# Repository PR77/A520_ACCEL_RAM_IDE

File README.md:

# A520_ACCEL_RAM_IDE
Amiga 500 in socket 68020 Accelerator, FastRAM and IDE Interface

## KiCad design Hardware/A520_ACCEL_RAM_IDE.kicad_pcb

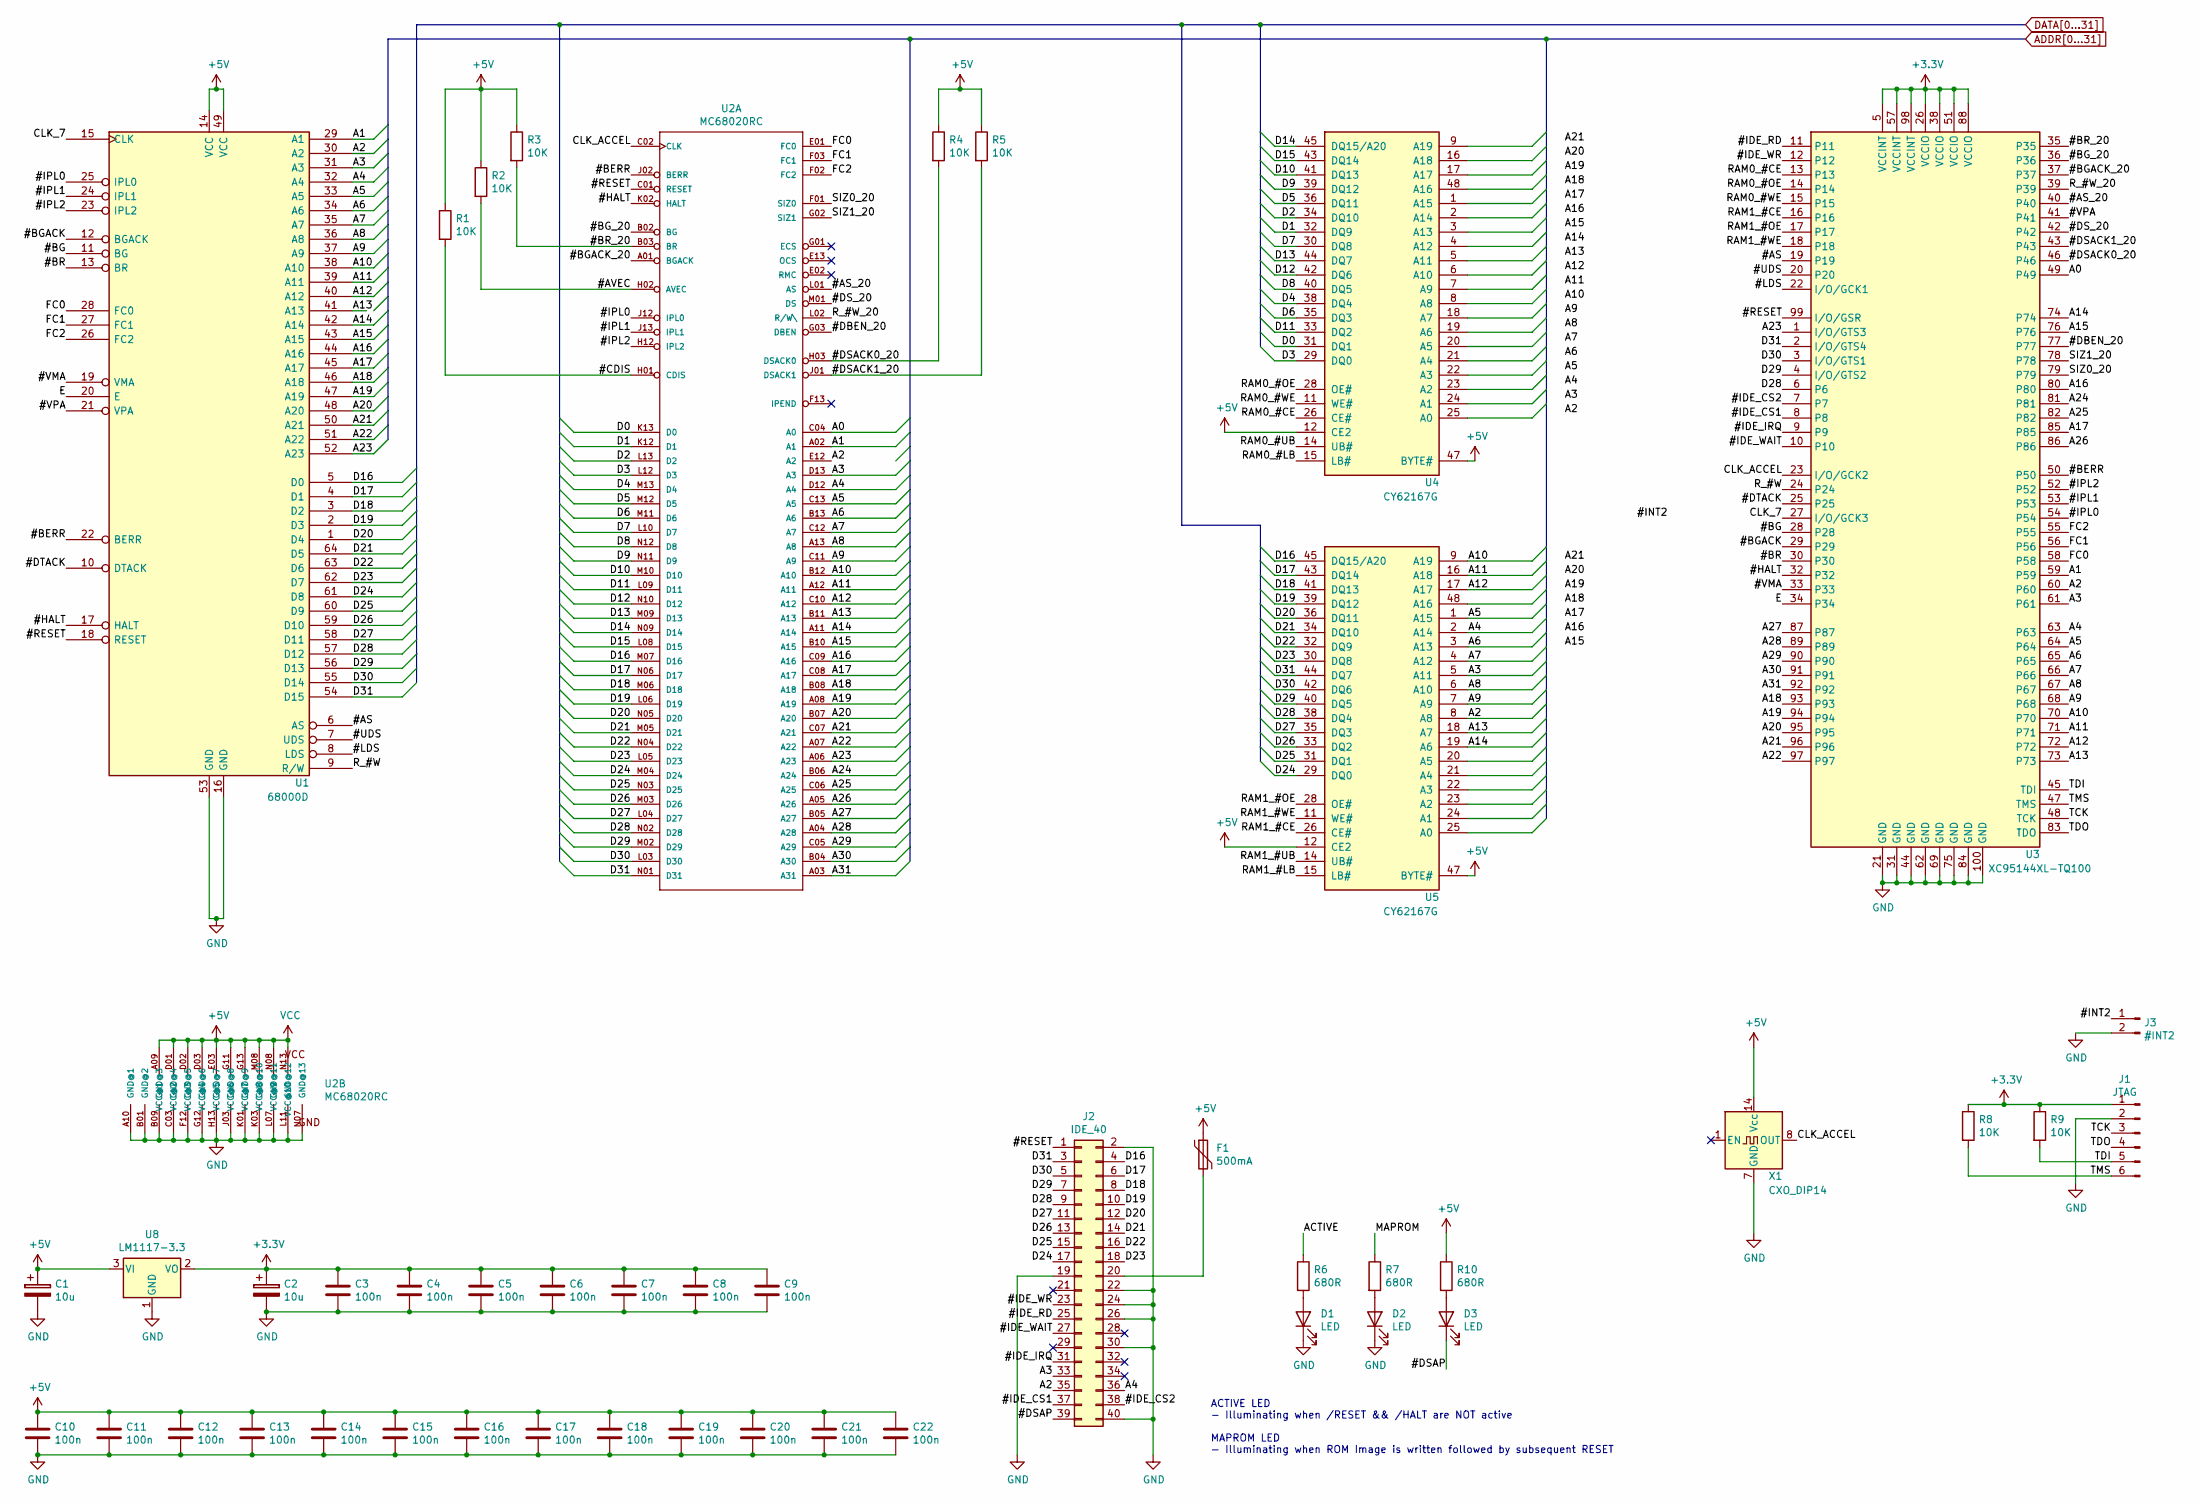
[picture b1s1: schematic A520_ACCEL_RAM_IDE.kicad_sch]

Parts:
C1, C2: 10u; CP_Tantalum_Case-B_EIA-3528-21_Hand
C3, C4, C5, C6, C7, C8, C9, C10, C11, C12, C13, C14, C15, C16, C17, C18, C19, C20, C21, C22: 100n; C_0805_HandSoldering
D1, D2, D3: LED; LED_0805_HandSoldering
F1: 500mA; R_1210_HandSoldering
J1: JTAG; Pin_Header_Straight_1x06_Pitch2.54mm
J2: IDE_40; PinHeader_2x20_P2.54mm_Horizontal
J3: #INT2; Pin_Header_Angled_1x02_Pitch2.54mm
R1, R2, R3, R4, R5, R8, R9: 10K; R_0805_HandSoldering
R6, R7, R10: 680R; R_0805_HandSoldering
U1: 68000D; DIP-64_W22.86mm_Socket_LongPads
U2: MC68020RC; micro-68x_db-MPGA114
U3: XC95144XL-TQ100; TQFP-100_14x14mm_P0.5mm
U4, U5: CY62167G; TSOP-I-48_18.4x12mm_P0.5mm
U8: LM1117-3.3; SOT-223-3_TabPin2
X1: CXO_DIP14; Oscillator_DIP-14

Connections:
+3V3: C2.1, C3.1, C4.1, C5.1, C6.1, C7.1, C8.1, C9.1, J1.1, R8.1, R9.1, U3.5 (VCCINT), U3.26 (VCCIO), U3.38 (VCCIO), U3.51 (VCCIO), U3.57 (VCCINT), U3.88 (VCCIO), U3.98 (VCCINT), U8.2 (VO)
+5V: C1.1, C10.1, C11.1, C12.1, C13.1, C14.1, C15.1, C16.1, C17.1, C18.1, C19.1, C20.1, C21.1, C22.1, F1.1, R1.1, R2.1, R3.1, R4.1, R5.1, R10.1, U1.14 (VCC), U1.49 (VCC), U2.A09 (VCC@1), U2.D01 (VCC@2), U2.D02 (VCC@3), U2.D03 (VCC@4), U2.E03 (VCC@5), U2.G11 (VCC@6), U2.G13 (VCC@7), U2.M08 (VCC@8), U2.N08 (VCC@9), U2.N13 (VCC@10), U4.12 (CE2), U4.37 (VCC), U4.47 (BYTE#), U5.12 (CE2), U5.37 (VCC), U5.47 (BYTE#), U8.3 (VI), X1.14 (Vcc)
/#AS: U1.6 (AS), U3.19
/#AS_20: U2.L01 (AS), U3.40
/#AVEC: R2.2, U2.H02 (AVEC)
/#BERR: U1.22 (BERR), U2.J02 (BERR), U3.50
/#BG: U1.11 (BG), U3.28
/#BGACK: U1.12 (BGACK), U3.29
/#BGACK_20: U2.A01 (BGACK), U3.37
/#BG_20: U2.B02 (BG), U3.36
/#BR: U1.13 (BR), U3.30
/#BR_20: R3.2, U2.B03 (BR), U3.35
/#CDIS: R1.2, U2.H01 (CDIS)
/#DBEN_20: U2.G03 (DBEN), U3.77
/#DSACK0_20: R4.2, U2.H03 (DSACK0), U3.46
/#DSACK1_20: R5.2, U2.J01 (DSACK1), U3.43
/#DSAP: D3.1 (K), J2.39
/#DS_20: U2.M01 (DS), U3.42
/#DTACK: U1.10 (DTACK), U3.25
/#HALT: U1.17 (HALT), U2.K02 (HALT), U3.32
/#IDE_CS1: J2.37, U3.8
/#IDE_CS2: J2.38, U3.7
/#IDE_IRQ: J2.31, U3.9
/#IDE_RD: J2.25, U3.11
/#IDE_WAIT: J2.27, U3.10
/#IDE_WR: J2.23, U3.12
/#INT2: J3.1
/#IPL0: U1.25 (IPL0), U2.J12 (IPL0), U3.54
/#IPL1: U1.24 (IPL1), U2.J13 (IPL1), U3.53
/#IPL2: U1.23 (IPL2), U2.H12 (IPL2), U3.52
/#LDS: U1.8 (LDS), U3.22 (I/O/GCK1)
/#RESET: J2.1, U1.18 (RESET), U2.C01 (RESET), U3.99 (I/O/GSR)
/#UDS: U1.7 (UDS), U3.20
/#VMA: U1.19 (VMA), U3.33
/#VPA: U1.21 (VPA), U3.41
/A0: U2.C04 (A0), U3.49
/A1: U1.29 (A1), U2.A02 (A1), U3.59
/A2: J2.35, U1.30 (A2), U2.E12 (A2), U3.60, U5.8 (A8)
/A3: J2.33, U1.31 (A3), U2.D13 (A3), U3.61, U5.5 (A11)
/A4: J2.36, U1.32 (A4), U2.D12 (A4), U3.63, U5.2 (A14)
/A5: U1.33 (A5), U2.C13 (A5), U3.64, U5.1 (A15)
/A6: U1.34 (A6), U2.B13 (A6), U3.65, U5.3 (A13)
/A7: U1.35 (A7), U2.C12 (A7), U3.66, U5.4 (A12)
/A8: U1.36 (A8), U2.A13 (A8), U3.67, U5.6 (A10)
/A9: U1.37 (A9), U2.C11 (A9), U3.68, U5.7 (A9)
/A10: U1.38 (A10), U2.B12 (A10), U3.70, U5.9 (A19)
/A11: U1.39 (A11), U2.A12 (A11), U3.71, U5.16 (A18)
/A12: U1.40 (A12), U2.C10 (A12), U3.72, U5.17 (A17)
/A13: U1.41 (A13), U2.B11 (A13), U3.73, U5.18 (A7)
/A14: U1.42 (A14), U2.A11 (A14), U3.74, U5.19 (A6)
/A15: U1.43 (A15), U2.B10 (A15), U3.76
/A16: U1.44 (A16), U2.C09 (A16), U3.80
/A17: U1.45 (A17), U2.C08 (A17), U3.85
/A18: U1.46 (A18), U2.B08 (A18), U3.93
/A19: U1.47 (A19), U2.A08 (A19), U3.94
/A20: U1.48 (A20), U2.B07 (A20), U3.95
/A21: U1.50 (A21), U2.C07 (A21), U3.96
/A22: U1.51 (A22), U2.A07 (A22), U3.97
/A23: U1.52 (A23), U2.A06 (A23), U3.1 (I/O/GTS3)
/A24: U2.B06 (A24), U3.81
/A25: U2.C06 (A25), U3.82
/A26: U2.A05 (A26), U3.86
/A27: U2.B05 (A27), U3.87
/A28: U2.A04 (A28), U3.89
/A29: U2.C05 (A29), U3.90
/A30: U2.B04 (A30), U3.91
/A31: U2.A03 (A31), U3.92
/ACTIVE: R6.1
/CLK_7: U1.15 (CLK), U3.27 (I/O/GCK3)
/CLK_ACCEL: U2.C02 (CLK), U3.23 (I/O/GCK2), X1.8 (OUT)
/D0: U2.K13 (D0), U4.31 (DQ1)
/D1: U2.K12 (D1), U4.32 (DQ9)
/D2: U2.L13 (D2), U4.34 (DQ10)
/D3: U2.L12 (D3), U4.29 (DQ0)
/D4: U2.M13 (D4), U4.38 (DQ4)
/D5: U2.M12 (D5), U4.36 (DQ11)
/D6: U2.M11 (D6), U4.35 (DQ3)
/D7: U2.L10 (D7), U4.30 (DQ8)
/D8: U2.N12 (D8), U4.40 (DQ5)
/D9: U2.N11 (D9), U4.39 (DQ12)
/D10: U2.M10 (D10), U4.41 (DQ13)
/D11: U2.L09 (D11), U4.33 (DQ2)
/D12: U2.N10 (D12), U4.42 (DQ6)
/D13: U2.M09 (D13), U4.44 (DQ7)
/D14: U2.N09 (D14), U4.45 (DQ15/A20)
/D15: U2.L08 (D15), U4.43 (DQ14)
/D16: J2.4, U1.5 (D0), U2.M07 (D16), U5.45 (DQ15/A20)
/D17: J2.6, U1.4 (D1), U2.N06 (D17), U5.43 (DQ14)
/D18: J2.8, U1.3 (D2), U2.M06 (D18), U5.41 (DQ13)
/D19: J2.10, U1.2 (D3), U2.L06 (D19), U5.39 (DQ12)
/D20: J2.12, U1.1 (D4), U2.N05 (D20), U5.36 (DQ11)
/D21: J2.14, U1.64 (D5), U2.M05 (D21), U5.34 (DQ10)
/D22: J2.16, U1.63 (D6), U2.N04 (D22), U5.32 (DQ9)
/D23: J2.18, U1.62 (D7), U2.L05 (D23), U5.30 (DQ8)
/D24: J2.17, U1.61 (D8), U2.M04 (D24), U5.29 (DQ0)
/D25: J2.15, U1.60 (D9), U2.N03 (D25), U5.31 (DQ1)
/D26: J2.13, U1.59 (D10), U2.M03 (D26), U5.33 (DQ2)
/D27: J2.11, U1.58 (D11), U2.L04 (D27), U5.35 (DQ3)
/D28: J2.9, U1.57 (D12), U2.N02 (D28), U3.6, U5.38 (DQ4)
/D29: J2.7, U1.56 (D13), U2.M02 (D29), U3.4 (I/O/GTS2), U5.40 (DQ5)
/D30: J2.5, U1.55 (D14), U2.L03 (D30), U3.3 (I/O/GTS1), U5.42 (DQ6)
/D31: J2.3, U1.54 (D15), U2.N01 (D31), U3.2 (I/O/GTS4), U5.44 (DQ7)
/E: U1.20 (E), U3.34
/FC0: U1.28 (FC0), U2.E01 (FC0), U3.58
/FC1: U1.27 (FC1), U2.F03 (FC1), U3.56
/FC2: U1.26 (FC2), U2.F02 (FC2), U3.55
/MAPROM: R7.1
/RAM0_#CE: U3.13, U4.26 (CE#)
/RAM0_#LB: U4.15 (LB#)
/RAM0_#OE: U3.14, U4.28 (OE#)
/RAM0_#UB: U4.14 (UB#)
/RAM0_#WE: U3.15, U4.11 (WE#)
/RAM1_#CE: U3.16, U5.26 (CE#)
/RAM1_#LB: U5.15 (LB#)
/RAM1_#OE: U3.17, U5.28 (OE#)
/RAM1_#UB: U5.14 (UB#)
/RAM1_#WE: U3.18, U5.11 (WE#)
/R_#W: U1.9 (R/W), U3.24
/R_#W_20: U2.L02 (R/W\), U3.39
/SIZ0_20: U2.F01 (SIZ0), U3.79
/SIZ1_20: U2.G02 (SIZ1), U3.78
/TCK: J1.3, U3.48 (TCK)
/TDI: J1.5, R9.2, U3.45 (TDI)
/TDO: J1.4, U3.83 (TDO)
/TMS: J1.6, R8.2, U3.47 (TMS)
GND: C1.2, C2.2, C3.2, C4.2, C5.2, C6.2, C7.2, C8.2, C9.2, C10.2, C11.2, C12.2, C13.2, C14.2, C15.2, C16.2, C17.2, C18.2, C19.2, C20.2, C21.2, C22.2, D1.1 (K), D2.1 (K), J1.2, J2.2, J2.19, J2.22, J2.24, J2.26, J2.30, J2.40, J3.2, U1.16 (GND), U1.53 (GND), U2.A10 (GND@1), U2.B01 (GND@2), U2.B09 (GND@3), U2.C03 (GND@4), U2.F12 (GND@5), U2.G12 (GND@6), U2.H13 (GND@7), U2.J03 (GND@8), U2.K01 (GND@9), U2.K03 (GND@10), U2.L07 (GND@11), U2.L11 (GND@12), U2.N07 (GND@13), U3.21 (GND), U3.31 (GND), U3.44 (GND), U3.62 (GND), U3.69 (GND), U3.75 (GND), U3.84 (GND), U3.100 (GND), U4.27 (GND), U4.46 (GND), U5.27 (GND), U5.46 (GND), U8.1 (GND), X1.7 (GND)
unnamed: D1.2 (A), R6.2
unnamed: D2.2 (A), R7.2
unnamed: D3.2 (A), R10.2
unnamed: F1.2, J2.20

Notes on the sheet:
ACTIVE LED - Illuminating when /RESET && /HALT are NOT active MAPROM LED - Illuminating when ROM Image is written followed by subsequent RESET

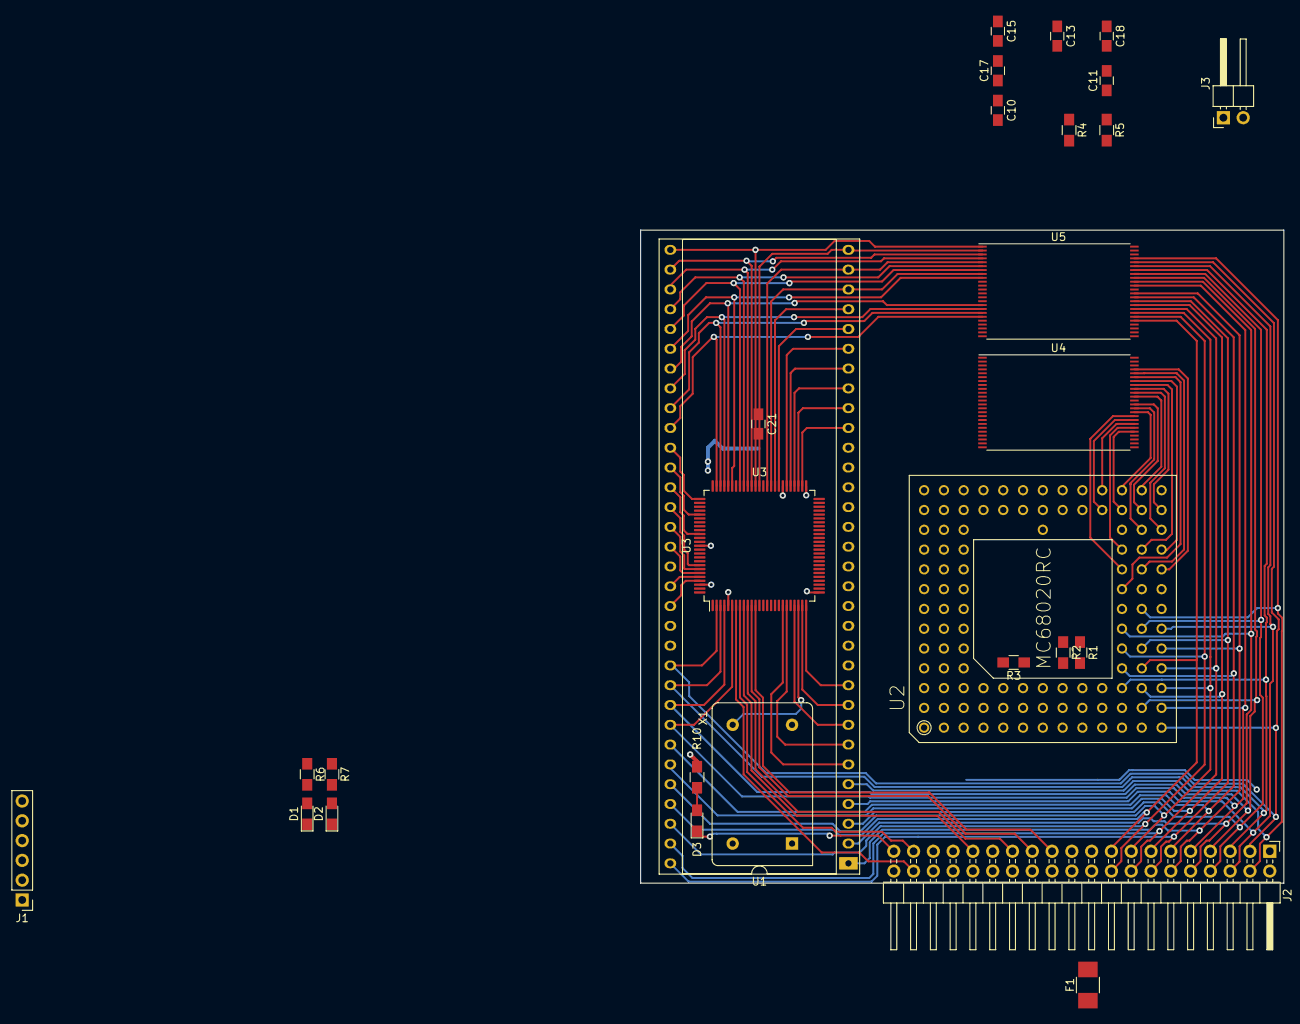
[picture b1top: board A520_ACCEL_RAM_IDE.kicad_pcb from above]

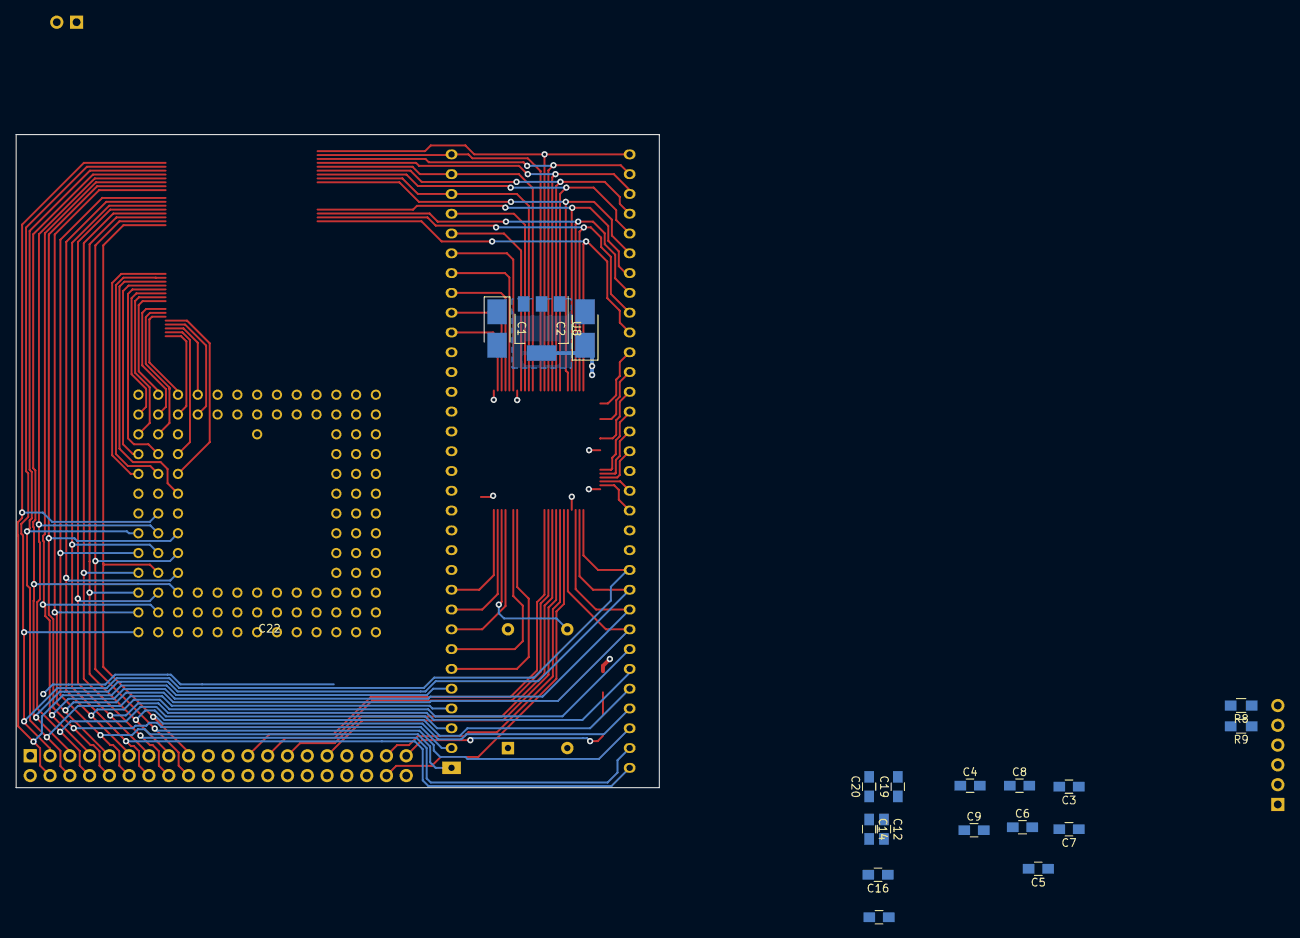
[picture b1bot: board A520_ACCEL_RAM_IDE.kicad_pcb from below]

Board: 4 copper layers, 82.6 x 83.8 mm, 46 parts (18 on the bottom side), 123 nets.

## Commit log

2022-06-22 Initial
2022-12-15 Initial layout proposal
